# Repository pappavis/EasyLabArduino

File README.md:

### EasyLab Arduino Robotauto
Arduino Robot alles-op-één bordje door **Michiel Erasmus** / EasyLab4Kids. Dit is die tegniese ontwerpe daarvan.<br/>

<br/>

Credits:
---
**Ontwerp** deur Michiel Erasmus<br/>
**Kontak** thebapodcast@gmail.com<br/>
**Voorbeelde** https://www.facebook.com/EasyBlocks4Kids/<br/>
<br/>

EasyLab basis
---
Wat maak die EasyLab so besonder?<br/>
 - Robotauto op die planeet **MARS!!**
 - Volledig praktyk getest op kinders in Nederland<br/>
 - Beskikbaar met online lesmateriaal in Zuid-Afrikaans en Nederlands<br/>
 
EasyLab tegniese moontlikhede
---
Vir mense met 'n computer brein..<br/>
 - Support vir 2x robotmotors<br/>
 - 1x servo aansluiting<br/>
 - 2x Lynvolg snesore aansluitinge
 - 7x koperplaat aansluiting om maklik 'goedkope' aliexpress-sensore te kan gebruik<br/>
 - Skroefverbindinge vir robotmotors<br/>
 - GPIO en IO-poorte is almal beskikbaar
 - Beskikbaar in twee smake: Arduino en Raspberry Pi<br/>
 <br/>
 Elke EasyLab wordt ambagtelik in Den Haag, Nederland gemaak deur personeel met 'n mentaal of fysieke beperking. Dit help mee aan 'n menswaardig bestaan.<br/>

Self probeer?
---
kyk dan op https://www.facebook.com/EasyBlocks4Kids/ <br/>
<br/>
**EasyLab4Kids met LCD skerm en afstandmeting sensor;**<br/>
<br/>
<br/>
**EasyLab nuusgierige by CoderDojo Den Haag, Nederland [Jun-2017]**<br/>
<br/>
<br/>
Wil jy ook 'n EasyLab? Kontak thebapodcast@gmail.com<br/>
<br/>
<br/>
#easylab4kids #easyblocks4kids #arduinorobot
<br/>

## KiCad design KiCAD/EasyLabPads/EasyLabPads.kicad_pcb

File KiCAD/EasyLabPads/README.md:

### decprecated. NIET gebruik.
Dit projek het verval. Moet dit nie gebruik.<br/>

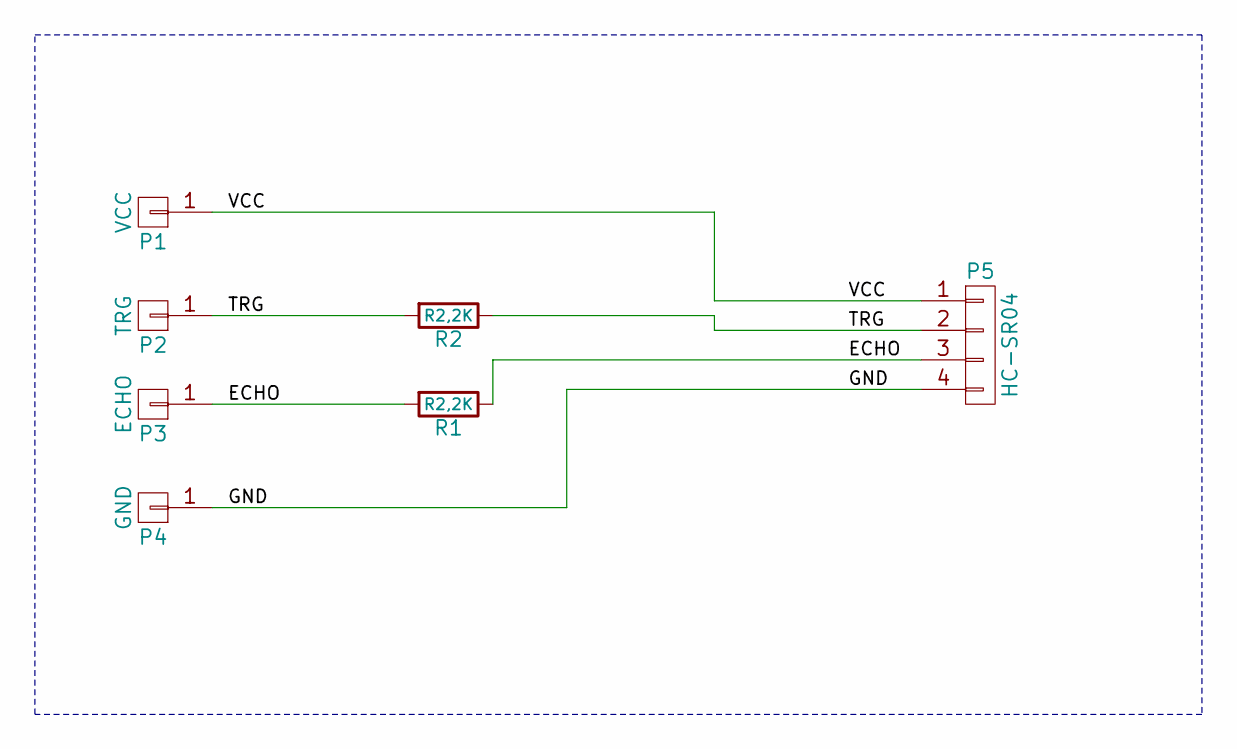
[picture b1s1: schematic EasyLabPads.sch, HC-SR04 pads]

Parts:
P1: VCC; z_BBC-BIT
P2: TRG; z_BBC-BIT
P3: ECHO; z_BBC-BIT
P4: GND; z_BBC-BIT
P5: HC-SR04; Pin_Header_Angled_1x04
R1, R2: R2,2K; Resistor_Vertical_RM5mm

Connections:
/ECHO: P3.1, P5.3, R1.1, R1.2
/GND: P4.1, P5.4
/TRG: P2.1, P5.2, R2.1, R2.2
/VCC: P1.1, P5.1

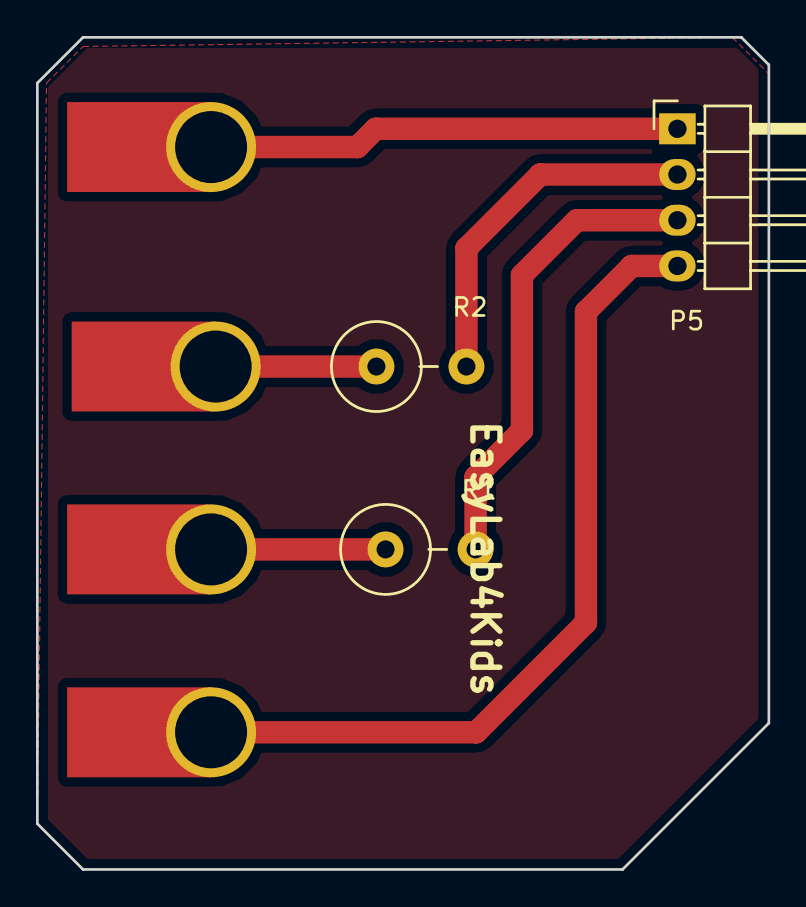
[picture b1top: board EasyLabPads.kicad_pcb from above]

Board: 2 copper layers, 40.6 x 46.2 mm, 7 parts (0 on the bottom side), 4 nets.

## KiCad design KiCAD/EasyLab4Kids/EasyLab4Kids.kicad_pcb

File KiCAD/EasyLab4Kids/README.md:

###EasyLab Arduino V1.0
Arduino Nano versie.

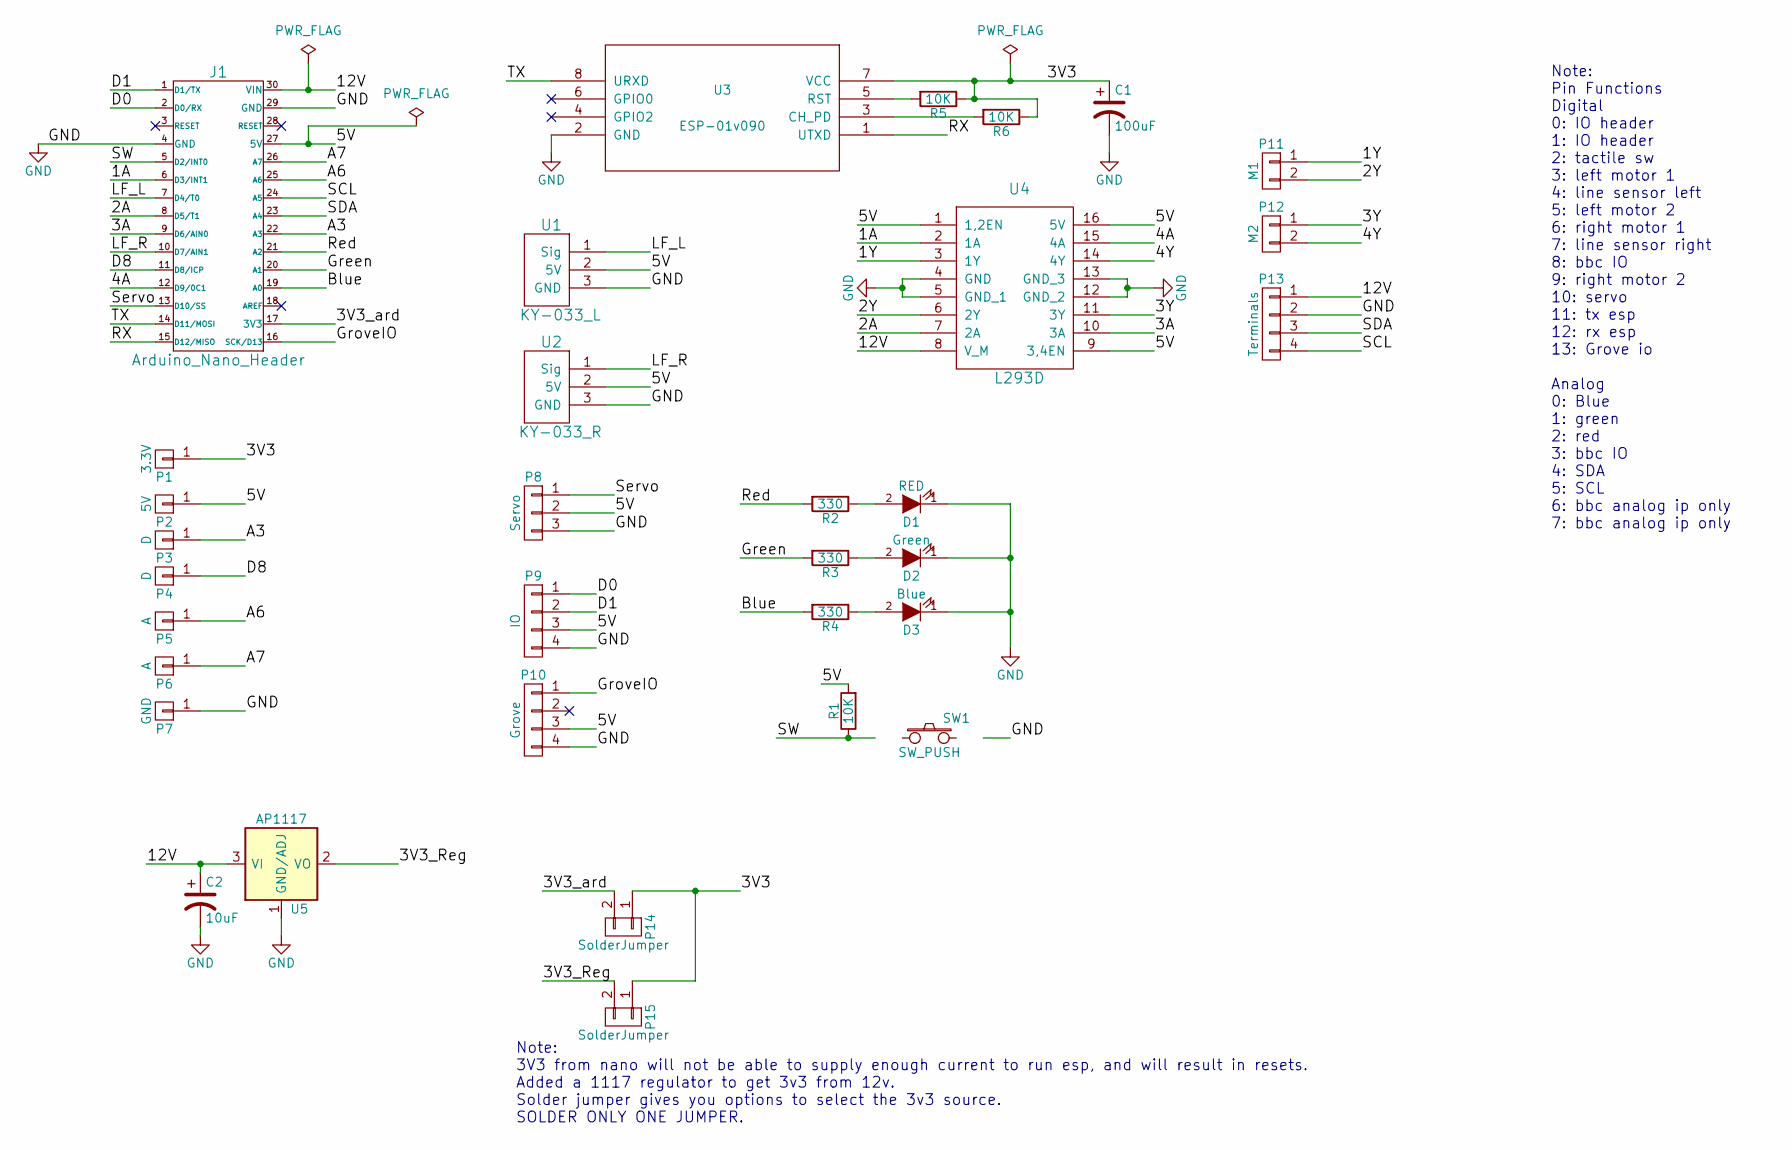
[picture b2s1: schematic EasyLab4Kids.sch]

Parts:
C1: 100uF; C_Radial_D5_L6_P2.5
C2: 10uF; C_Radial_D5_L6_P2.5
D1: RED; LED-5MM
D2: Green; LED-5MM
D3: Blue; LED-5MM
J1: Arduino_Nano_Header; arduino_nano_header
P1: 3.3V; z_BBC-BIT
P2: 5V; z_BBC-BIT
P3, P4: D; z_BBC-BIT
P5, P6: A; z_BBC-BIT
P7: GND; z_BBC-BIT
P8: Servo; Pin_Header_Straight_1x03
P9: IO; Pin_Header_Straight_1x04
P10: Grove; grove_1x04
P11: M1; mkds_1,5-2
P12: M2; mkds_1,5-2
P13: Terminals; mkds_1,5-4
P14, P15: SolderJumper; R_0603
R1, R5, R6: 10K; Resistor_Horizontal_RM10mm
R2, R3, R4: 330; Resistor_Horizontal_RM10mm
SW1: SW_PUSH; PCB_PUSH_edit
U1: KY-033_L; Pin_Header_Straight_1x03
U2: KY-033_R; Pin_Header_Straight_1x03
U3: ESP-01v090; ESP-01_SilkScreen
U4: L293D; DIP-16__300_ELL
U5: AP1117; SOT-223

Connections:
/1A: J1.6 (D3/INT1), U4.2 (1A)
/1Y: P11.1, U4.3 (1Y)
/2A: J1.8 (D5/T1), U4.7 (2A)
/2Y: P11.2, U4.6 (2Y)
/3A: J1.9 (D6/AIN0), U4.10 (3A)
/3V3: C1.1, P1.1, P14.1, P15.1, R5.1, R6.1, U3.7 (VCC)
/3V3_Reg: P15.2, U5.2 (VO), U5.4 (VO)
/3V3_ard: J1.17 (3V3), P14.2
/3Y: P12.1, U4.11 (3Y)
/4A: J1.12 (D9/0C1), U4.15 (4A)
/4Y: P12.2, U4.14 (4Y)
/5V: J1.27 (5V), P2.1, P8.2, P9.3, P10.3, R1.2, U1.2 (5V), U2.2 (5V), U4.1 (1,2EN), U4.9 (3,4EN), U4.16 (5V)
/12V: C2.1, J1.30 (VIN), P13.1, U4.8 (V_M), U5.3 (VI)
/A3: J1.22 (A3), P3.1
/A6: J1.25 (A6), P5.1
/A7: J1.26 (A7), P6.1
/Blue: J1.19 (A0), R4.2
/D0: J1.2 (D0/RX), P9.1
/D1: J1.1 (D1/TX), P9.2
/D8: J1.11 (D8/ICP), P4.1
/Green: J1.20 (A1), R3.2
/GroveIO: J1.16 (SCK/D13), P10.1
/LF_L: J1.7 (D4/T0), U1.1 (Sig)
/LF_R: J1.10 (D7/AIN1), U2.1 (Sig)
/RX: J1.15 (D12/MISO), U3.1 (UTXD)
/Red: J1.21 (A2), R2.2
/SCL: J1.24 (A5), P13.4
/SDA: J1.23 (A4), P13.3
/SW: J1.5 (D2/INT0), R1.1, SW1.1
/Servo: J1.13 (D10/SS), P8.1
/TX: J1.14 (D11/MOSI), U3.8 (URXD)
GND: C1.2, C2.2, D1.1 (K), D2.1 (K), D3.1 (K), J1.4 (GND), J1.29 (GND), P7.1, P8.3, P9.4, P10.4, P13.2, SW1.2, U1.3 (GND), U2.3 (GND), U3.2 (GND), U4.4 (GND), U4.5 (GND_1), U4.12 (GND_2), U4.13 (GND_3), U5.1 (GND/ADJ)
unnamed: D1.2 (A), R2.1
unnamed: D2.2 (A), R3.1
unnamed: D3.2 (A), R4.1
unnamed: R5.2, U3.5 (RST)
unnamed: R6.2, U3.3 (CH_PD)

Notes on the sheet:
Note: Pin Functions Digital 0: IO header 1: IO header 2: tactile sw 3: left motor 1 4: line sensor left 5: left motor 2 6: right motor 1 7: line sensor right 8: bbc IO 9: right motor 2 10: servo 11: tx esp 12: rx esp 13: Grove io Analog 0: Blue 1: green 2: red 3: bbc IO 4: SDA 5: SCL 6: bbc analog 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
Note: 3V3 from nano will not be able to supply enough current to run esp, and will result in resets. Added a 1117 regulator to get 3v3 from 12v. Solder jumper gives you options to select the 3v3 source. SOLDER ONLY ONE JUMPER.

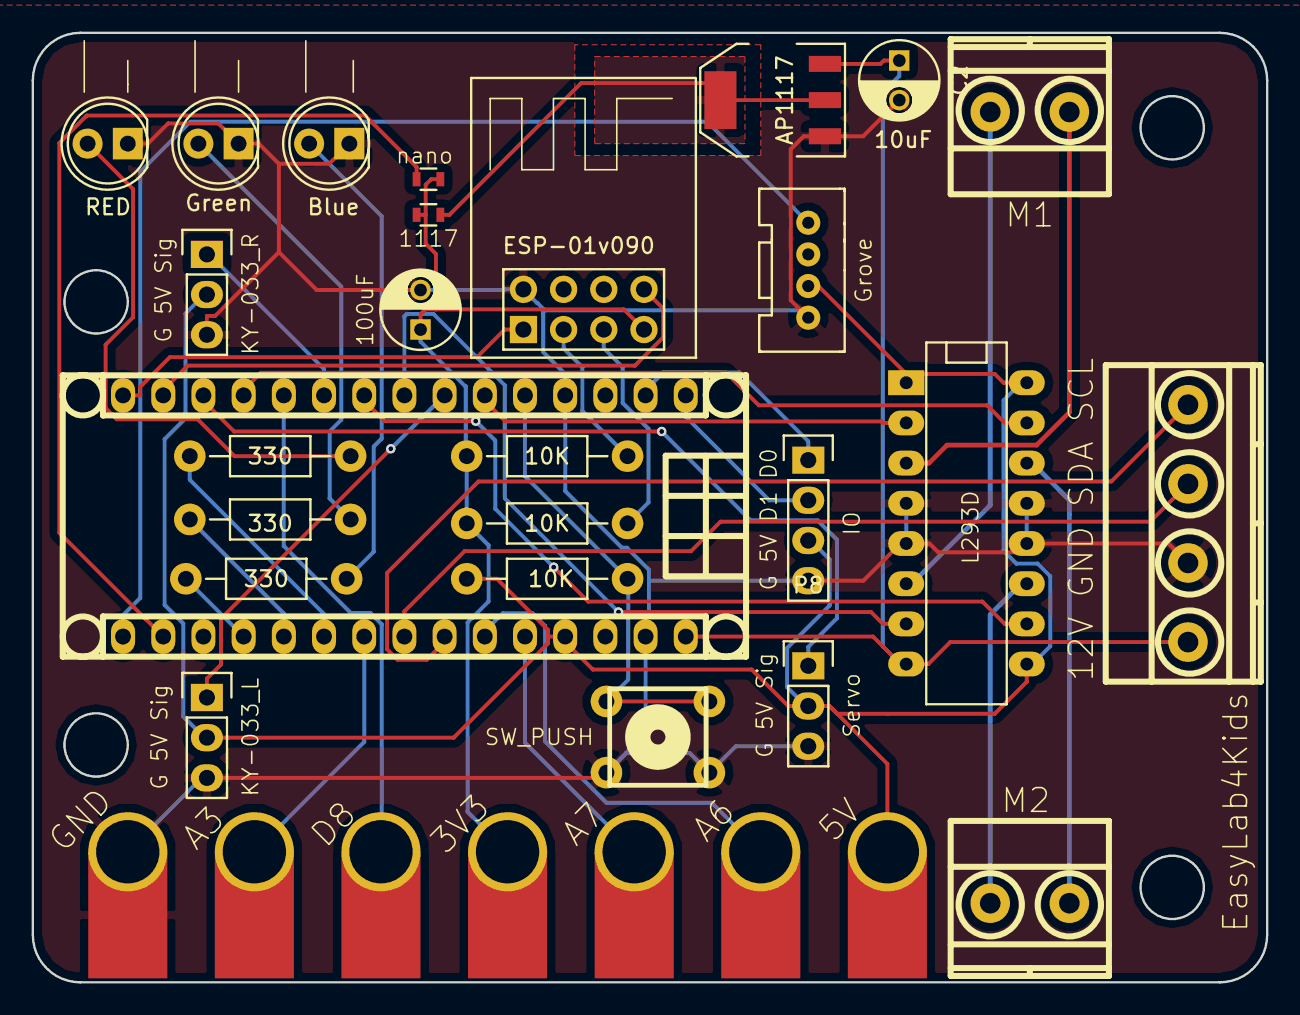
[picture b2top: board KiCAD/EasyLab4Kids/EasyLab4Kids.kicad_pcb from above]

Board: 2 copper layers, 78.0 x 60.0 mm, 33 parts (0 on the bottom side), 37 nets.

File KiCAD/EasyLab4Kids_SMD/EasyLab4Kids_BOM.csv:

"Id";"Designator";"Behuizing";"Hoeveelheid";"Orientatie";"Leverancier en ref";
1;"P11";"mkds_1,5-2";1;"M1";;;
2;"C1";"C_0805_HandSoldering";1;"100uF";;;
3;"C2";"C_0805_HandSoldering";1;"10uF/16V";;;
4;"C3";"C_0805_HandSoldering";1;"10uF";;;
5;"D1";"LED-5MM";1;"Red";;;
6;"D2";"LED-5MM";1;"Green";;;
7;"D3";"LED-5MM";1;"Blue";;;
8;"J1";"arduino_nano_header";1;"Arduino_Nano_Header";;;
9;"P8";"Pin_Header_Straight_1x03";1;"Servo";;;
10;"P9";"Pin_Header_Straight_1x04";1;"IO";;;
11;"P10";"grove_1x04";1;"Grove";;;
12;"P12";"mkds_1,5-2";1;"M2";;;
13;"P13";"mkds_1,5-2";1;"PWR IN";;;
14;"R1,R5,R6";"C_0805_HandSoldering";3;"10K";;;
15;"R2,R3,R4";"C_0805_HandSoldering";3;"330";;;
16;"SW1";"PCB_PUSH_edit";1;"SW_PUSH";;;
17;"U1";"Pin_Header_Straight_1x03";1;"KY-033_L";;;
18;"U2";"Pin_Header_Straight_1x03";1;"KY-033_R";;;
19;"U5";"SOT-223";1;"AP1117";;;
20;"P1";"BBC_CONNECTOR";1;"3.3V";;;
21;"P2";"BBC_CONNECTOR";1;"5V";;;
22;"P3,P4,P16,P17";"BBC_CONNECTOR";4;"D";;;
23;"P5,P6";"BBC_CONNECTOR";2;"A";;;
24;"P7";"BBC_CONNECTOR";1;"GND";;;
25;"P14,P15";"SolderJumper";2;"SolderJumper";;;
26;"U3";"ESP-01_SilkScreen";1;"ESP-01v090";;;
27;"U4";"SOIC-20_7.5x12.8mm_Pitch1.27mm";1;"L293D_SMD";;;

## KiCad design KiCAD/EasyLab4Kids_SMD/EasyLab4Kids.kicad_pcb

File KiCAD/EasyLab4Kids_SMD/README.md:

EasyLab SMD-versie<br/>

Credits:
---
Ontwerp door Michiel Erasmus<br/>

<br/>

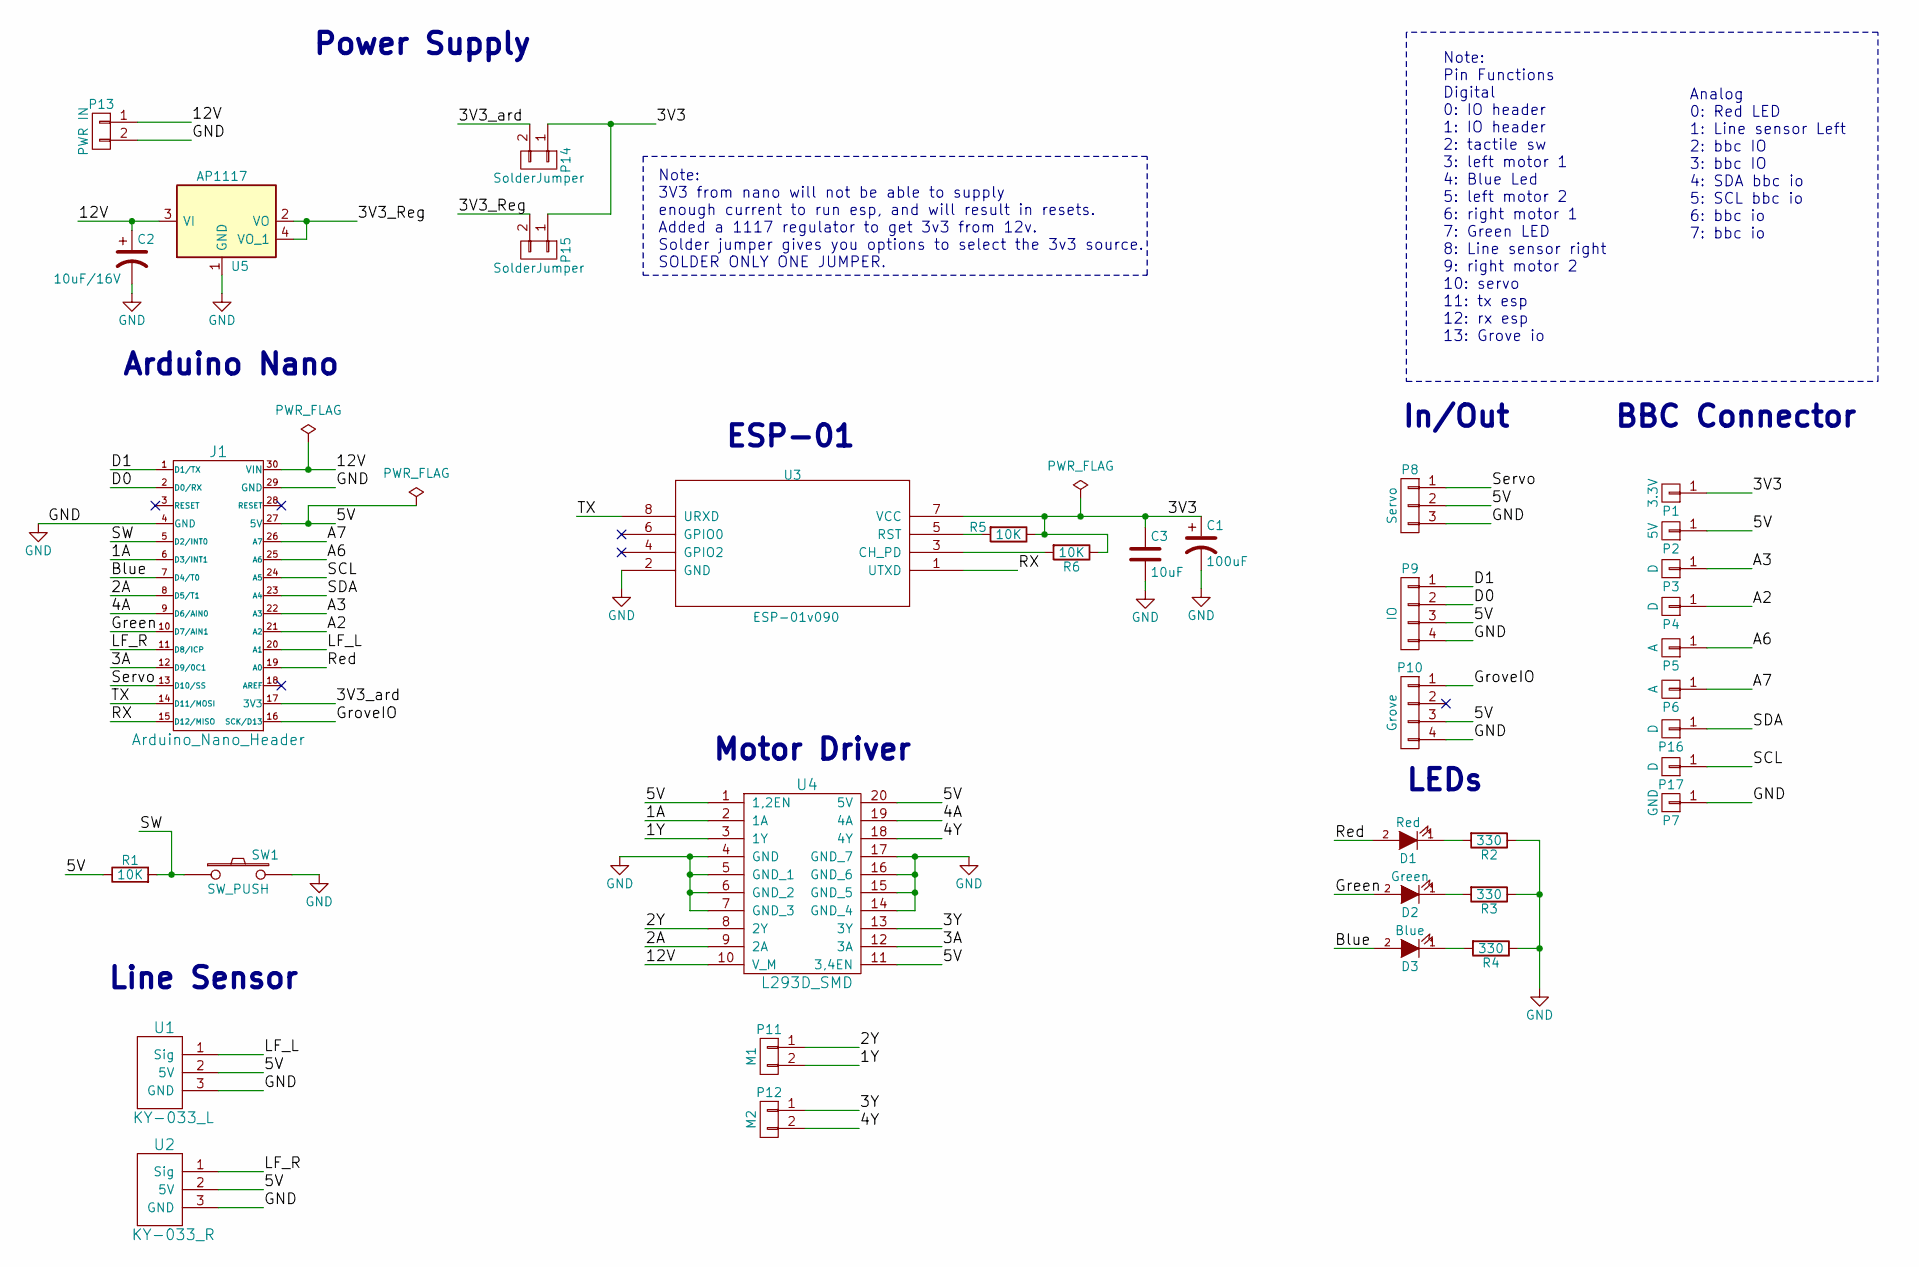
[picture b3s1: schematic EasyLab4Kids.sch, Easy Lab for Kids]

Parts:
C1: 100uF; C_0805_HandSoldering
C2: 10uF/16V; C_0805_HandSoldering
C3: 10uF; C_0805_HandSoldering
D1: Red; LED-5MM
D2: Green; LED-5MM
D3: Blue; LED-5MM
J1: Arduino_Nano_Header; arduino_nano_header
P1: 3.3V; BBC_CONNECTOR
P2: 5V; BBC_CONNECTOR
P3, P4, P16, P17: D; BBC_CONNECTOR
P5, P6: A; BBC_CONNECTOR
P7: GND; BBC_CONNECTOR
P8: Servo; Pin_Header_Straight_1x03
P9: IO; Pin_Header_Straight_1x04
P10: Grove; grove_1x04
P11: M1; mkds_1,5-2
P12: M2; mkds_1,5-2
P13: PWR IN; mkds_1,5-2
P14, P15: SolderJumper
R1, R5, R6: 10K; C_0805_HandSoldering
R2, R3, R4: 330; C_0805_HandSoldering
SW1: SW_PUSH; PCB_PUSH_edit
U1: KY-033_L; Pin_Header_Straight_1x03
U2: KY-033_R; Pin_Header_Straight_1x03
U3: ESP-01v090; ESP-01_SilkScreen
U4: L293D_SMD; SOIC-20_7.5x12.8mm_Pitch1.27mm
U5: AP1117; SOT-223

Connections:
/1A: J1.6 (D3/INT1), U4.2 (1A)
/1Y: P11.2, U4.3 (1Y)
/2A: J1.8 (D5/T1), U4.9 (2A)
/2Y: P11.1, U4.8 (2Y)
/3A: J1.12 (D9/0C1), U4.12 (3A)
/3V3: C1.1, C3.1, P1.1, P14.1, P15.1, R5.1, R6.1, U3.7 (VCC)
/3V3_Reg: P15.2, U5.2 (VO), U5.4 (VO_1)
/3V3_ard: J1.17 (3V3), P14.2
/3Y: P12.1, U4.13 (3Y)
/4A: J1.9 (D6/AIN0), U4.19 (4A)
/4Y: P12.2, U4.18 (4Y)
/5V: J1.27 (5V), P2.1, P8.2, P9.3, P10.3, R1.1, U1.2 (5V), U2.2 (5V), U4.1 (1,2EN), U4.11 (3,4EN), U4.20 (5V)
/12V: C2.1, J1.30 (VIN), P13.1, U4.10 (V_M), U5.3 (VI)
/A2: J1.21 (A2), P4.1
/A3: J1.22 (A3), P3.1
/A6: J1.25 (A6), P5.1
/A7: J1.26 (A7), P6.1
/Blue: D3.2 (A), J1.7 (D4/T0)
/D0: J1.2 (D0/RX), P9.2
/D1: J1.1 (D1/TX), P9.1
/Green: D2.2 (A), J1.10 (D7/AIN1)
/GroveIO: J1.16 (SCK/D13), P10.1
/LF_L: J1.20 (A1), U1.1 (Sig)
/LF_R: J1.11 (D8/ICP), U2.1 (Sig)
/RX: J1.15 (D12/MISO), U3.1 (UTXD)
/Red: D1.2 (A), J1.19 (A0)
/SCL: J1.24 (A5), P17.1
/SDA: J1.23 (A4), P16.1
/SW: J1.5 (D2/INT0), R1.2, SW1.1
/Servo: J1.13 (D10/SS), P8.1
/TX: J1.14 (D11/MOSI), U3.8 (URXD)
GND: C1.2, C2.2, C3.2, J1.4 (GND), J1.29 (GND), P7.1, P8.3, P9.4, P10.4, P13.2, R2.1, R3.1, R4.1, SW1.2, U1.3 (GND), U2.3 (GND), U3.2 (GND), U4.4 (GND), U4.5 (GND_1), U4.6 (GND_2), U4.7 (GND_3), U4.14 (GND_4), U4.15 (GND_5), U4.16 (GND_6), U4.17 (GND_7), U5.1 (GND)
unnamed: D1.1 (K), R2.2
unnamed: D2.1 (K), R3.2
unnamed: D3.1 (K), R4.2
unnamed: R5.2, U3.5 (RST)
unnamed: R6.2, U3.3 (CH_PD)

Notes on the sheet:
Note: Pin Functions Digital 0: IO header 1: IO header 2: tactile sw 3: left motor 1 4: Blue Led 5: left motor 2 6: right motor 1 7: Green LED 8: Line sensor right 9: right motor 2 10: servo 11: tx esp 12: rx esp 13: Grove io
Note: 3V3 from nano will not be able to supply enough current to run esp, and will result in resets. Added a 1117 regulator to get 3v3 from 12v. Solder jumper gives you options to select the 3v3 source. SOLDER ONLY ONE JUMPER.
Power Supply
Arduino Nano
ESP-01
Line Sensor
Motor Driver
BBC Connector
In/Out
Analog 0: Red LED 1: Line sensor Left 2: bbc IO 3: bbc IO 4: SDA bbc io 5: SCL bbc io 6: bbc io 7: bbc io
LEDs

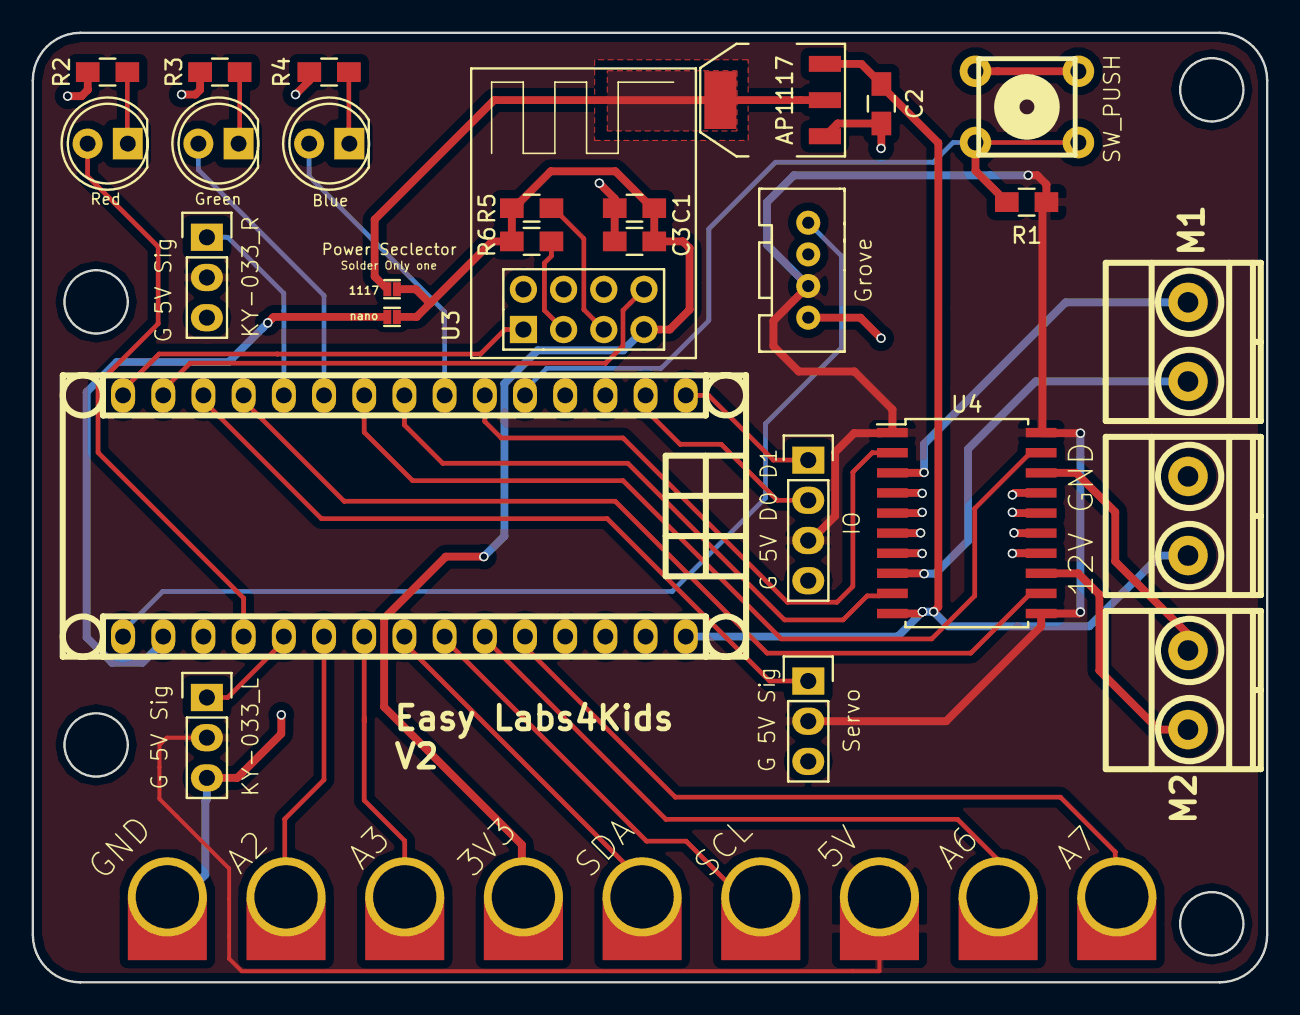
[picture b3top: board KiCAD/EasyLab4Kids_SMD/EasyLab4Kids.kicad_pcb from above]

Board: 2 copper layers, 78.0 x 60.0 mm, 36 parts (0 on the bottom side), 37 nets.

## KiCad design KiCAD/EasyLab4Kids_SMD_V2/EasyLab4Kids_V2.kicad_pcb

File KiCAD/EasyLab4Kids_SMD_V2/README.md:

EasyLab V2  -- 13-01-2018
---
<br/>
Arduino robot uitbreidingsbord.<br/>
<br/>
Verbeterde  Arduino versie;<br/>
 - 6DOF sensor support<br/>
 - Onboard zoemer<br/>
 - Onboard L923D robot aansturing
 - Arduino nano
<br/>
**Credits:**<br/>
 - Layout -- Hemal Chevli @fiverr<br/>
 - Ontwerp en spesifikasies -- Michiel Erasmus<br/>
<br/>
<br/>

<br/>
EasyLab v2 met MPU-6050 sensor.

<br/>
Copyrights:<br/>
©2018 EasyLab4Kids en Michiel Erasmus
<br/>

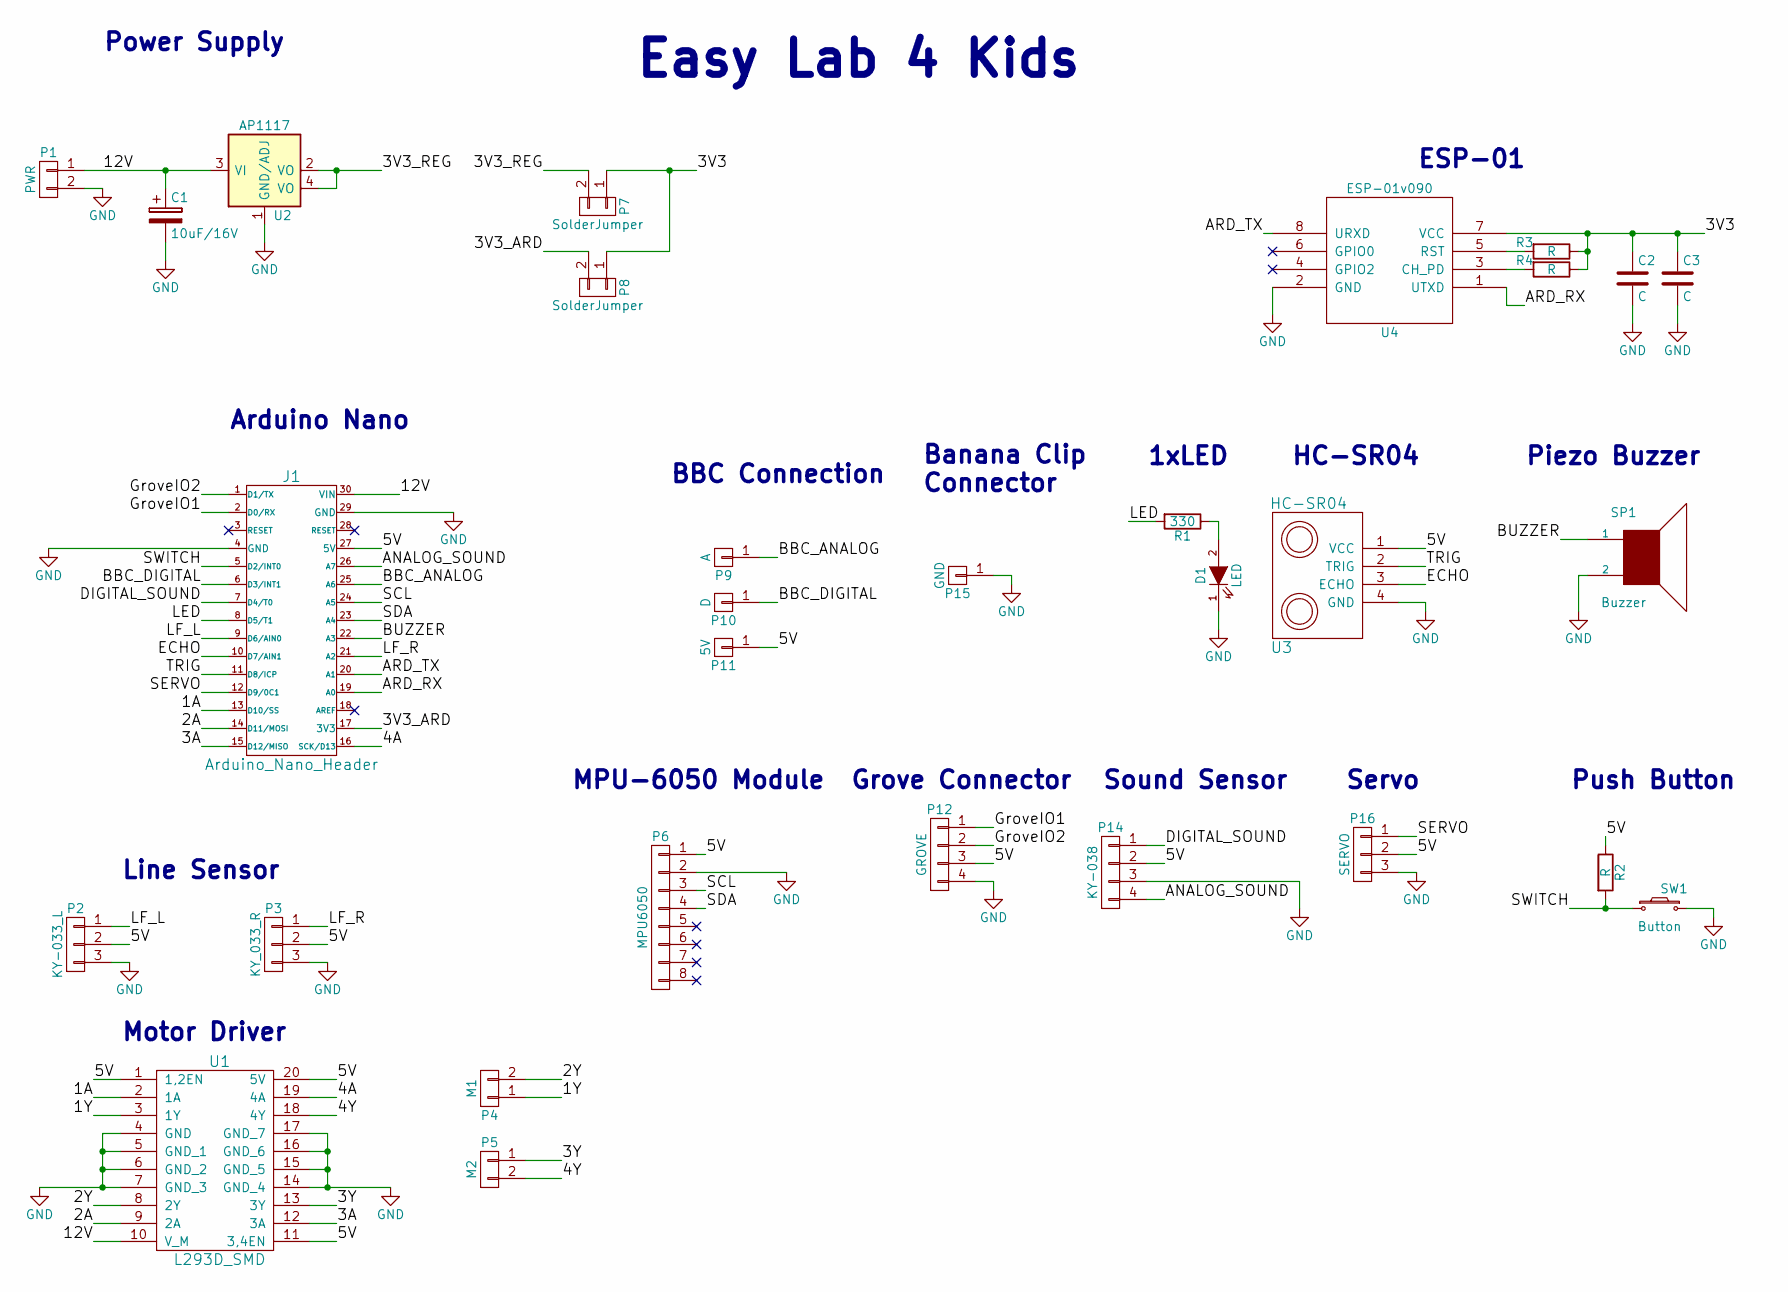
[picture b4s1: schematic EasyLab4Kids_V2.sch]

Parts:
C1: 10uF/16V; C_0805_HandSoldering
C2, C3: C; C_0805_HandSoldering
D1: LED; LED-5MM
J1: Arduino_Nano_Header; arduino_nano_header
P1: PWR; mkds_1,5-2
P2: KY-033_L; Pin_Header_Straight_1x03
P3: KY_033_R; Pin_Header_Straight_1x03
P4: M1; mkds_1,5-2
P5: M2; mkds_1,5-2
P6: MPU6050; MPU-6050
P7, P8: SolderJumper
P9: A; BBC_CONNECTOR
P10: D; BBC_CONNECTOR
P11: 5V; BBC_CONNECTOR
P12: GROVE; grove_1x04
P14: KY-038; Pin_Header_Straight_1x04
P15: GND; Makey_conn_3.2mm
P16: SERVO; Pin_Header_Straight_1x03
R1: 330; R_1206_HandSoldering
R2, R3, R4: R; R_1206_HandSoldering
SP1: Buzzer; Buzzer_12x9.5RM7.6
SW1: Button; PCB_PUSH_edit
U1: L293D_SMD; SOIC-20_7.5x12.8mm_Pitch1.27mm
U2: AP1117; SOT-223
U3: HC-SR04; Pin_Header_Straight_1x04
U4: ESP-01v090; ESP-01_SilkScreen

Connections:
/1A: J1.13 (D10/SS), U1.2 (1A)
/1Y: P4.1, U1.3 (1Y)
/2A: J1.14 (D11/MOSI), U1.9 (2A)
/2Y: P4.2, U1.8 (2Y)
/3A: J1.15 (D12/MISO), U1.12 (3A)
/3V3: C2.1, C3.1, P7.1, P8.1, R3.1, R4.1, U4.7 (VCC)
/3V3_ARD: J1.17 (3V3), P8.2
/3V3_REG: P7.2, U2.2 (VO), U2.4 (VO)
/3Y: P5.1, U1.13 (3Y)
/4A: J1.16 (SCK/D13), U1.19 (4A)
/4Y: P5.2, U1.18 (4Y)
/5V: J1.27 (5V), P2.2, P3.2, P6.1, P11.1, P12.3, P14.2, P16.2, R2.1, U1.1 (1,2EN), U1.11 (3,4EN), U1.20 (5V), U3.1 (VCC)
/12V: C1.1, J1.30 (VIN), P1.1, U1.10 (V_M), U2.3 (VI)
/ANALOG_SOUND: J1.26 (A7), P14.4
/ARD_RX: J1.19 (A0), U4.1 (UTXD)
/ARD_TX: J1.20 (A1), U4.8 (URXD)
/BBC_ANALOG: J1.25 (A6), P9.1
/BBC_DIGITAL: J1.6 (D3/INT1), P10.1
/BUZZER: J1.22 (A3), SP1.1
/DIGITAL_SOUND: J1.7 (D4/T0), P14.1
/ECHO: J1.10 (D7/AIN1), U3.3 (ECHO)
/GroveIO1: J1.2 (D0/RX), P12.1
/GroveIO2: J1.1 (D1/TX), P12.2
/LED: J1.8 (D5/T1), R1.2
/LF_L: J1.9 (D6/AIN0), P2.1
/LF_R: J1.21 (A2), P3.1
/SCL: J1.24 (A5), P6.3
/SDA: J1.23 (A4), P6.4
/SERVO: J1.12 (D9/0C1), P16.1
/SWITCH: J1.5 (D2/INT0), R2.2, SW1.1
/TRIG: J1.11 (D8/ICP), U3.2 (TRIG)
GND: C1.2, C2.2, C3.2, D1.1 (K), J1.4 (GND), J1.29 (GND), P1.2, P2.3, P3.3, P6.2, P12.4, P14.3, P15.1, P16.3, SP1.2, SW1.2, U1.4 (GND), U1.5 (GND_1), U1.6 (GND_2), U1.7 (GND_3), U1.14 (GND_4), U1.15 (GND_5), U1.16 (GND_6), U1.17 (GND_7), U2.1 (GND/ADJ), U3.4 (GND), U4.2 (GND)
unnamed: D1.2 (A), R1.1
unnamed: R3.2, U4.5 (RST)
unnamed: R4.2, U4.3 (CH_PD)

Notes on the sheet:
Easy Lab 4 Kids
Power Supply
Arduino Nano
Line Sensor
Motor Driver
ESP-01
BBC Connection
Banana Clip Connector
1xLED
HC-SR04
Piezo Buzzer
MPU-6050 Module
Grove Connector
Sound Sensor
Servo
Push Button

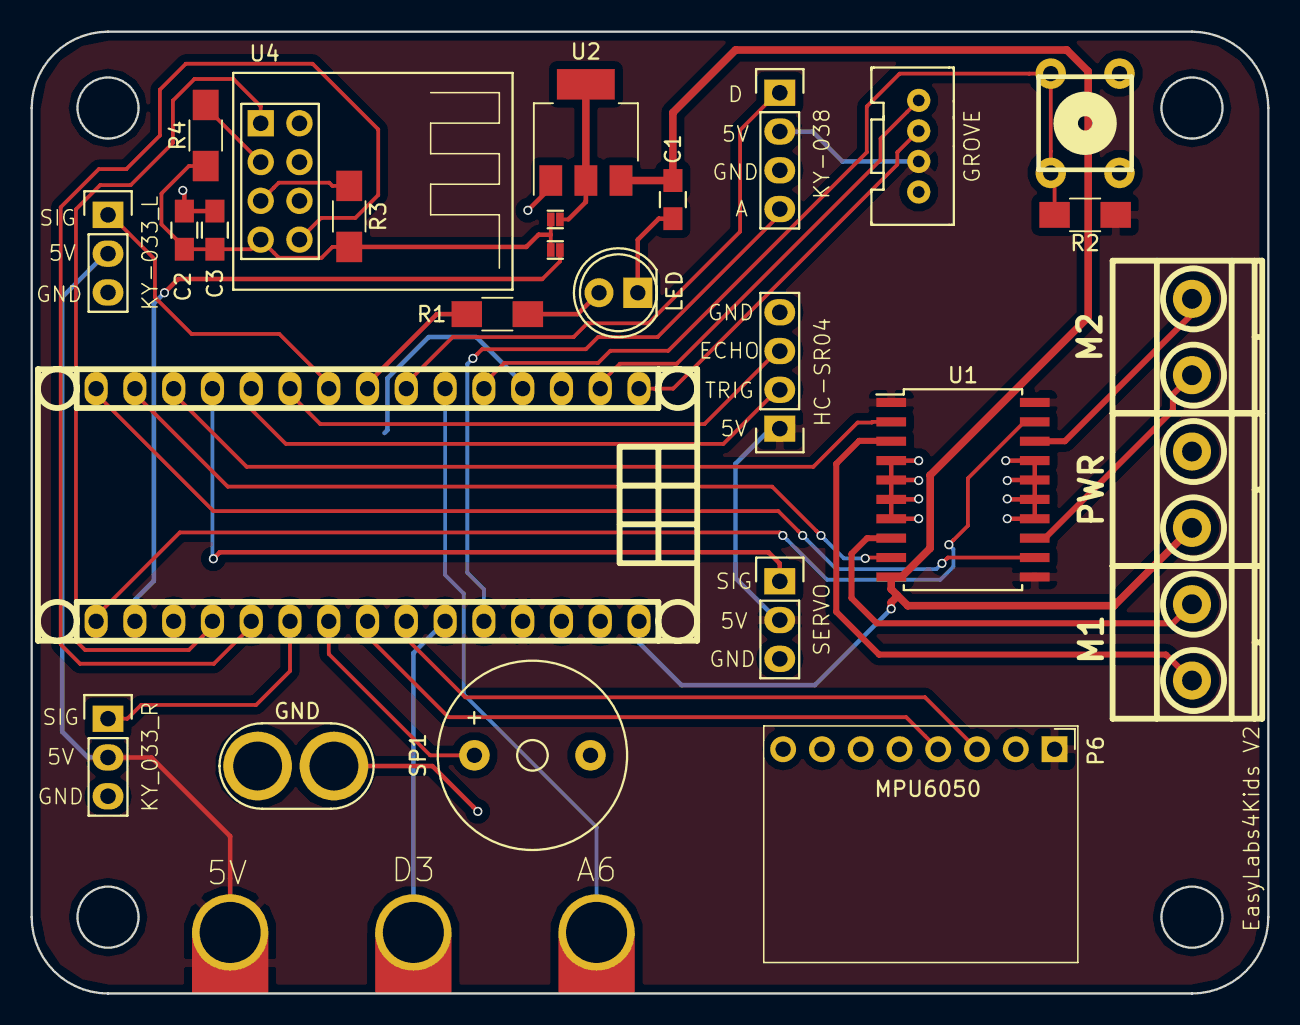
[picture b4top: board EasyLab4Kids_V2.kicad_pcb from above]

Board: 2 copper layers, 81.0 x 63.0 mm, 30 parts (0 on the bottom side), 35 nets.

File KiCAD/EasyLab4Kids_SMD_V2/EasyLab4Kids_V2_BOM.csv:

Title,EasyLab4Kids_V2
Revision,
Date,2018-01-13
Generated,13-1-2018 22:47:05
Company,
Comment 1,https://www.fiverr.com/users/hemalchevli/
Comment 2,Drawn By: Hemal Chevli
Comment 3,
Comment 4,
Total Parts,30
Total Unique Parts,26



Ref,Qty,Value,Footprint,
C2 C3 ,2,C,EasyLabs4Kids:C_0805_HandSoldering
C1 ,1,10uF/16V,EasyLabs4Kids:C_0805_HandSoldering
D1 ,1,LED,EasyLabs4Kids:LED-5MM
J1 ,1,Arduino_Nano_Header,EasyLabs4Kids:arduino_nano_header
P1 ,1,PWR,EasyLabs4Kids:mkds_1,5-2
P9 ,1,A,EasyLabs4Kids:BBC_CONNECTOR
P10 ,1,D,EasyLabs4Kids:BBC_CONNECTOR
P11 ,1,5V,EasyLabs4Kids:BBC_CONNECTOR
P15 ,1,GND,EasyLabs4Kids:Makey_conn_3.2mm
P16 ,1,SERVO,EasyLabs4Kids:Pin_Header_Straight_1x03
P14 ,1,KY-038,EasyLabs4Kids:Pin_Header_Straight_1x04
P12 ,1,GROVE,EasyLabs4Kids:grove_1x04
P2 ,1,KY-033_L,EasyLabs4Kids:Pin_Header_Straight_1x03
P3 ,1,KY_033_R,EasyLabs4Kids:Pin_Header_Straight_1x03
P6 ,1,MPU6050,EasyLabs4Kids:MPU-6050
P8 P7 ,2,SolderJumper,EasyLabs4Kids:SolderJumper
P4 ,1,M1,EasyLabs4Kids:mkds_1,5-2
P5 ,1,M2,EasyLabs4Kids:mkds_1,5-2
R1 ,1,330,Resistors_SMD:R_1206_HandSoldering
R3 R4 R2 ,3,R,Resistors_SMD:R_1206_HandSoldering
SP1 ,1,Buzzer,EasyLabs4Kids:Buzzer_12x9.5RM7.6
SW1 ,1,Button,EasyLabs4Kids:PCB_PUSH_edit
U4 ,1,ESP-01v090,EasyLabs4Kids:ESP-01_SilkScreen
U3 ,1,HC-SR04,EasyLabs4Kids:Pin_Header_Straight_1x04
U1 ,1,L293D_SMD,EasyLabs4Kids:SOIC-20_7.5x12.8mm_Pitch1.27mm
U2 ,1,AP1117,TO_SOT_Packages_SMD:SOT-223




BOM made with KICAD_BOM_WIZARD (https://github.com/HashDefineElectronics/KiCad_BOM_Wizard.git)
Generated 13-1-2018 22:47:05

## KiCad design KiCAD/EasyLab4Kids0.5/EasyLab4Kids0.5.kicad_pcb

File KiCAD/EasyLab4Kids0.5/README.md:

### EasyLab 0.5
prototype versie 0.5 ontwerp van **Michiel Erasmus**
<br/>

NIET GEBRUIKEN, dont use. Dit is 'n ou versie. <br/>

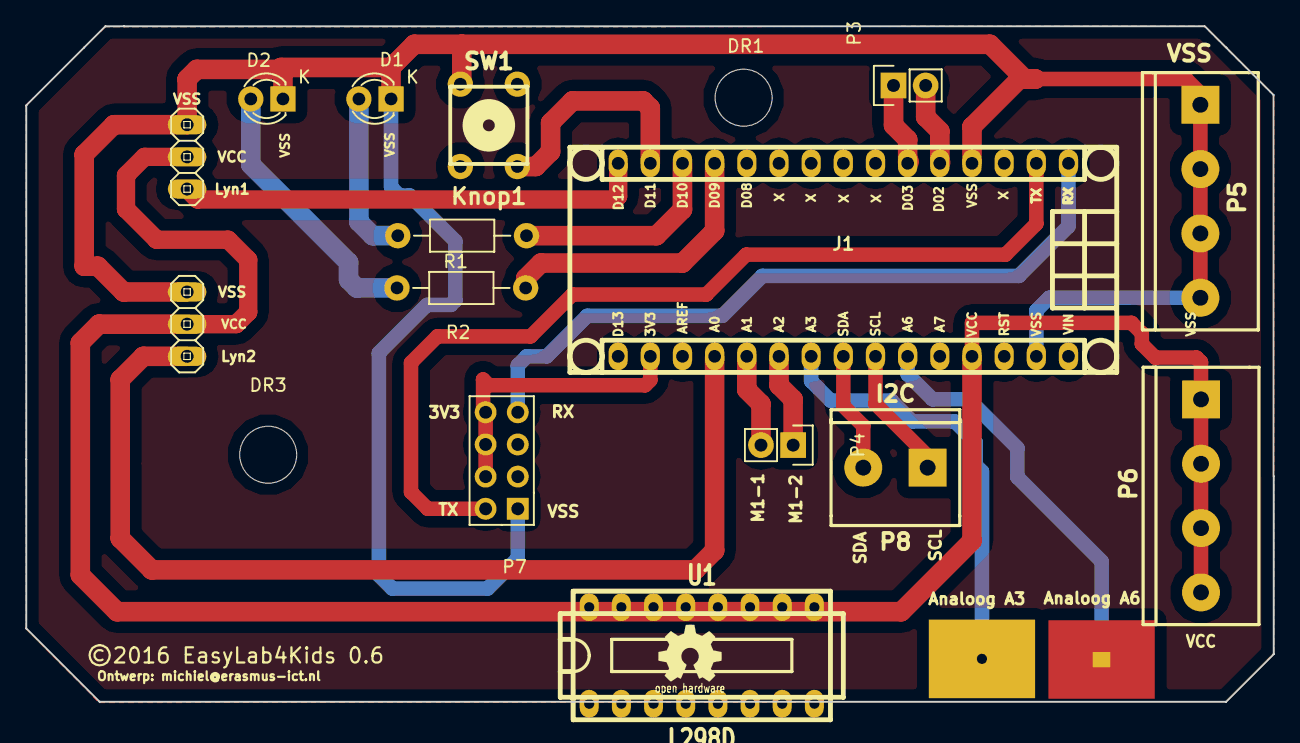
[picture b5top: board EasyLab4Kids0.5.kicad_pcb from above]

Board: 2 copper layers, 98.5 x 53.3 mm, 21 parts (1 on the bottom side), 20 nets.

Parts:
D1: LED-G; LED-3MM
D2: LED-R; LED-3MM
DR1: gat1; MountingHole_4.5mm
DR2: CE-LOGO1; Logo_silk_OSHW_6x6mm
DR3: gat2; MountingHole_4.5mm
DR4: Koperplaat A3; EasyPad-8mm
DR5: Logo2; oshw_silkscreen_3
DR6: Koperplaat A6; EasyPad-8mm
J1: Arduino_Nano_Header; arduino_nano_header
P1: KY-033-L; pinhead-1-1X03
P2: KY-033-R; pinhead-1-1X03
P3: MOTOR-R; Pin_Header_Straight_1x02
P4: MOTOR-L; Pin_Header_Straight_1x02
P5: VSS; mors_4p
P6: VCC; mors_4p
P7: ESP8266; ESP-01
P8: I2C; mors_2p
R1, R2: R1k; Resistor_Horizontal_RM10mm
SW1: Knop1; PCB_PUSH
U1: L298D; dil_16-300_socket

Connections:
/3V3: J1.17, P7.4, P7.6, P7.8
/A3: DR4.1, J1.22
/A6: DR6.1, J1.25
/Knop1: J1.14, SW1.2
/LED-G: J1.12, R2.1
/LED-R: J1.13, R1.1
/LYN1: J1.15, P2.1
/LYN2: J1.19, P1.1
/M1-1: J1.20, P4.2, U1.8
/M1-2: J1.21, P4.1, U1.4
/M2-1: J1.6, P3.1
/M2-2: J1.5, P3.2
/SCL: J1.24, P8.1
/SDA: J1.23, P8.2
/VCC: J1.27, P1.2, P2.2, P6.1, P6.2, P6.3, P6.4, U1.5, U1.9
/VSS: D1.1, D2.1, J1.4, J1.29, P1.3, P2.3, P5.1, P5.2, P5.3, P5.4, P7.1, SW1.1, U1.7, U1.11
/Wifi-RX: J1.1, P7.7
/Wifi-TX: J1.2, P7.2
unnamed: D1.2, R1.2
unnamed: D2.2, R2.2

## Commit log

2018-04-05 :tada: Added .gitattributes & .gitignore files
2018-04-05 eerste commit
2018-04-05 bygewerkt

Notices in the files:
KiCAD/EasyLab4Kids/EasyLab4Kids.sch:
©2017 EasyLab4Kids.nl
KiCAD/EasyLab4Kids0.5/EasyLab4Kids0.5.kicad_pcb:
©2016 EasyLab4Kids
©2016 EasyLab4Kids 0.6
KiCAD/EasyLab4Kids_SMD_V2/EasyLab4Kids_V2.sch:
©2018 by EasyLab4Kids
